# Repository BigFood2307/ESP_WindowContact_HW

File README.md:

# ESP_WindowContact_HW
The HW for the Window Contact

References parts:

* SMD Resitor 10K - R3 
* SMD Resitor 330 - R2
* SMD Resitor 47k - R1
* SMD 4070 4 XOR - IC at the bottom

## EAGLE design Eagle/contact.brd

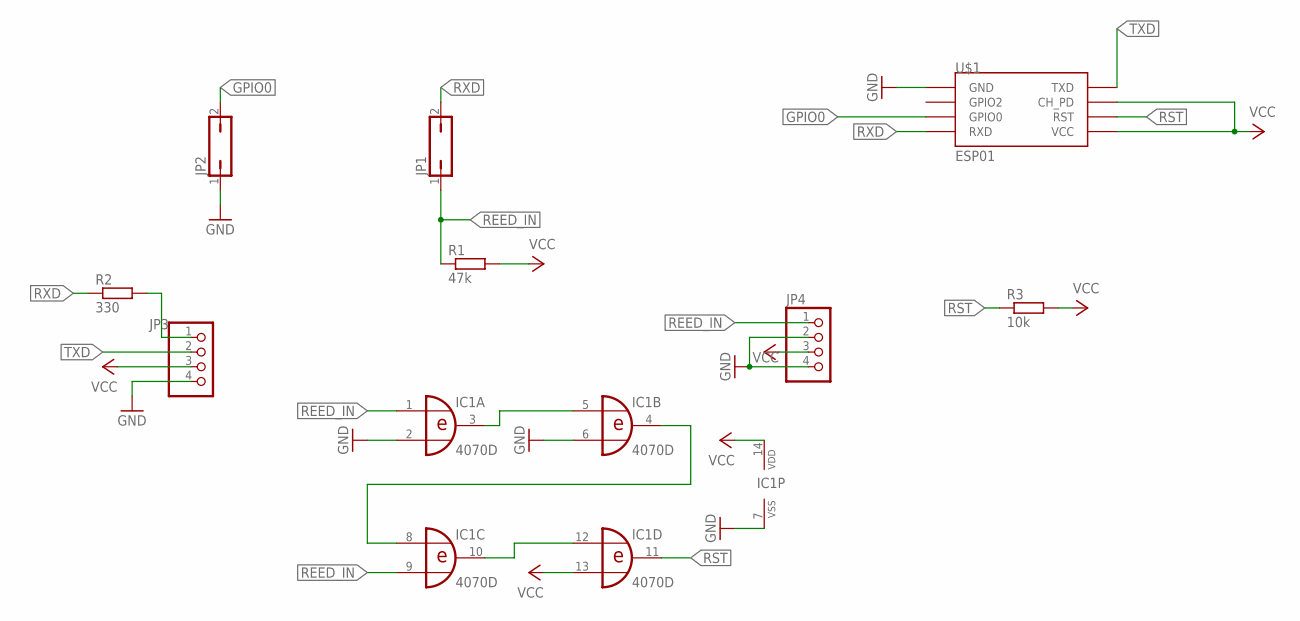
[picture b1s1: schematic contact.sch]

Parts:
IC1: 4070D; SO14
JP1, JP2: JP1Q; JP1
JP3, JP4: PINHD-1X4; 1X04
R1: 47k; R0805
R2: 330; R0805
R3: 10k; R0805
U$1: ESP01

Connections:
GND: IC1.2 (I1), IC1.6 (I1), IC1.7 (VSS), JP2.1, JP3.4, JP4.2, JP4.4, U$1.GND
GPIO0: JP2.2, U$1.GPIO0
unnamed: JP3.1, R2.2
unnamed: IC1.4 (O), IC1.8 (I0)
unnamed: IC1.3 (O), IC1.5 (I0)
unnamed: IC1.10 (O), IC1.12 (I0)
REED_IN: IC1.1 (I0), IC1.9 (I1), JP1.1, JP4.1, R1.1
RST: IC1.11 (O), R3.1, U$1.RST
RXD: JP1.2, R2.1, U$1.RX (RXD)
TXD: JP3.2, U$1.TX (TXD)
VCC: IC1.13 (I1), IC1.14 (VDD), JP3.3, JP4.3, R1.2, R3.2, U$1.CH_PD, U$1.VCC

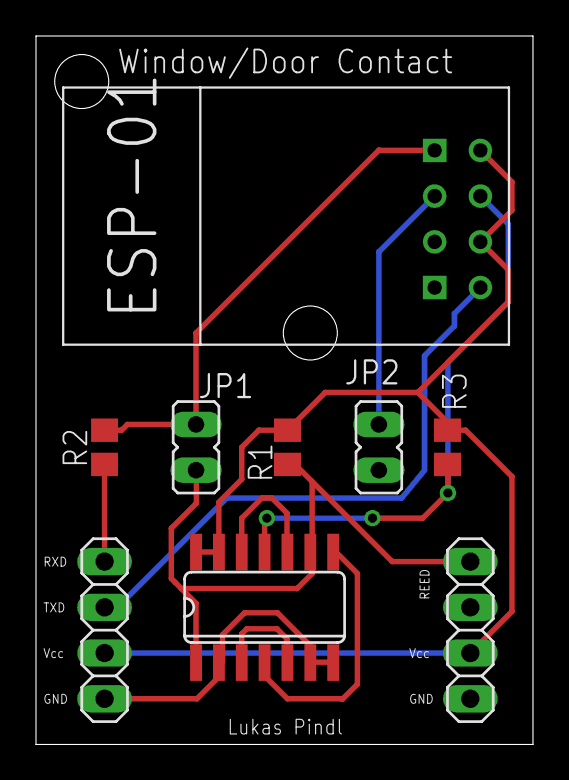
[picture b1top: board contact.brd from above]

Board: 2 copper layers, 27.6 x 39.4 mm, 9 parts (0 on the bottom side), 11 nets.

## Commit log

2022-07-24 Initial commit for HW
